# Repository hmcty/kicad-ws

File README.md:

# KiCad Workspace

This repository contains various KiCad hardware projects with an automated webviewer deployment.

## Projects

All KiCad projects are located in the `boards/` directory:
- `pedal_split_supply` - Pedal Split Supply

## Webviewer

An interactive webviewer is automatically built and deployed to GitHub Pages on every push to `main`.

**View the projects:** [https://hmcty.github.io/kicad-ws/](https://hmcty.github.io/kicad-ws/)

The webviewer allows you to:
- Browse all projects in the repository
- View schematics and PCB layouts interactively
- Download project files as ZIP archives
- Share links to specific locations in designs

## Deployment

The webviewer is built using [KiShare](https://github.com/hmcty/kishare) with [KiCanvas](https://github.com/theacodes/kicanvas) for rendering.

The deployment workflow (`.github/workflows/deploy.yml`) automatically:
1. Scans the repository for KiCad projects
2. Generates an interactive webviewer
3. Deploys to GitHub Pages

To trigger a manual rebuild, go to **Actions** → **Build and Deploy KiCad Webviewer** → **Run workflow**.

## Adding New Projects

Simply add new KiCad projects to the `boards/` directory and push to `main`. The webviewer will automatically rebuild and include the new projects.

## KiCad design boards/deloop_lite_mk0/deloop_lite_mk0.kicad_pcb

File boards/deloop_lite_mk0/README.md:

# Deloop Lite

System board for a simple, 2-track loop pedal.

Components:
- [Daisy Seed](https://electro-smith.com/products/daisy-seed)
  - Module carrying STM32H7 microcontroller, PCM3060 audio codec, and external
    SDRAM IC
- Barrel jack port assuming center-negative 9V DC power input
- +/-7V Power Supply
  - Imported design from a previous project, see [Pedal Split Supply](/#/project/pedal_split_supply)
- 2x 1/4" mono jacks (1 line-in, 1 line-out)
- 1x 3.5mm TRS MIDI input
- 2x audio input buffer (OPA2134)
- 2x audio output buffer (TL072)
- 1x output mix stage (TL072)
- 40-pin IDC header for UI and digital control connections
- 8x JST XH socket for auxiliary audio connections
- MicroSD card slot

The board is intended can be paired with different UI boards. Default signaling
assumes:
- 16x2 character LCD display
- Individually addressable RGB chain
- 3x footswitches
- 3x potentiometers (for track mixing)
- 1x rotary encoder (for menu navigation)
- 3x SPST switches

The board was designed to fit within a 1590DD enclosure.

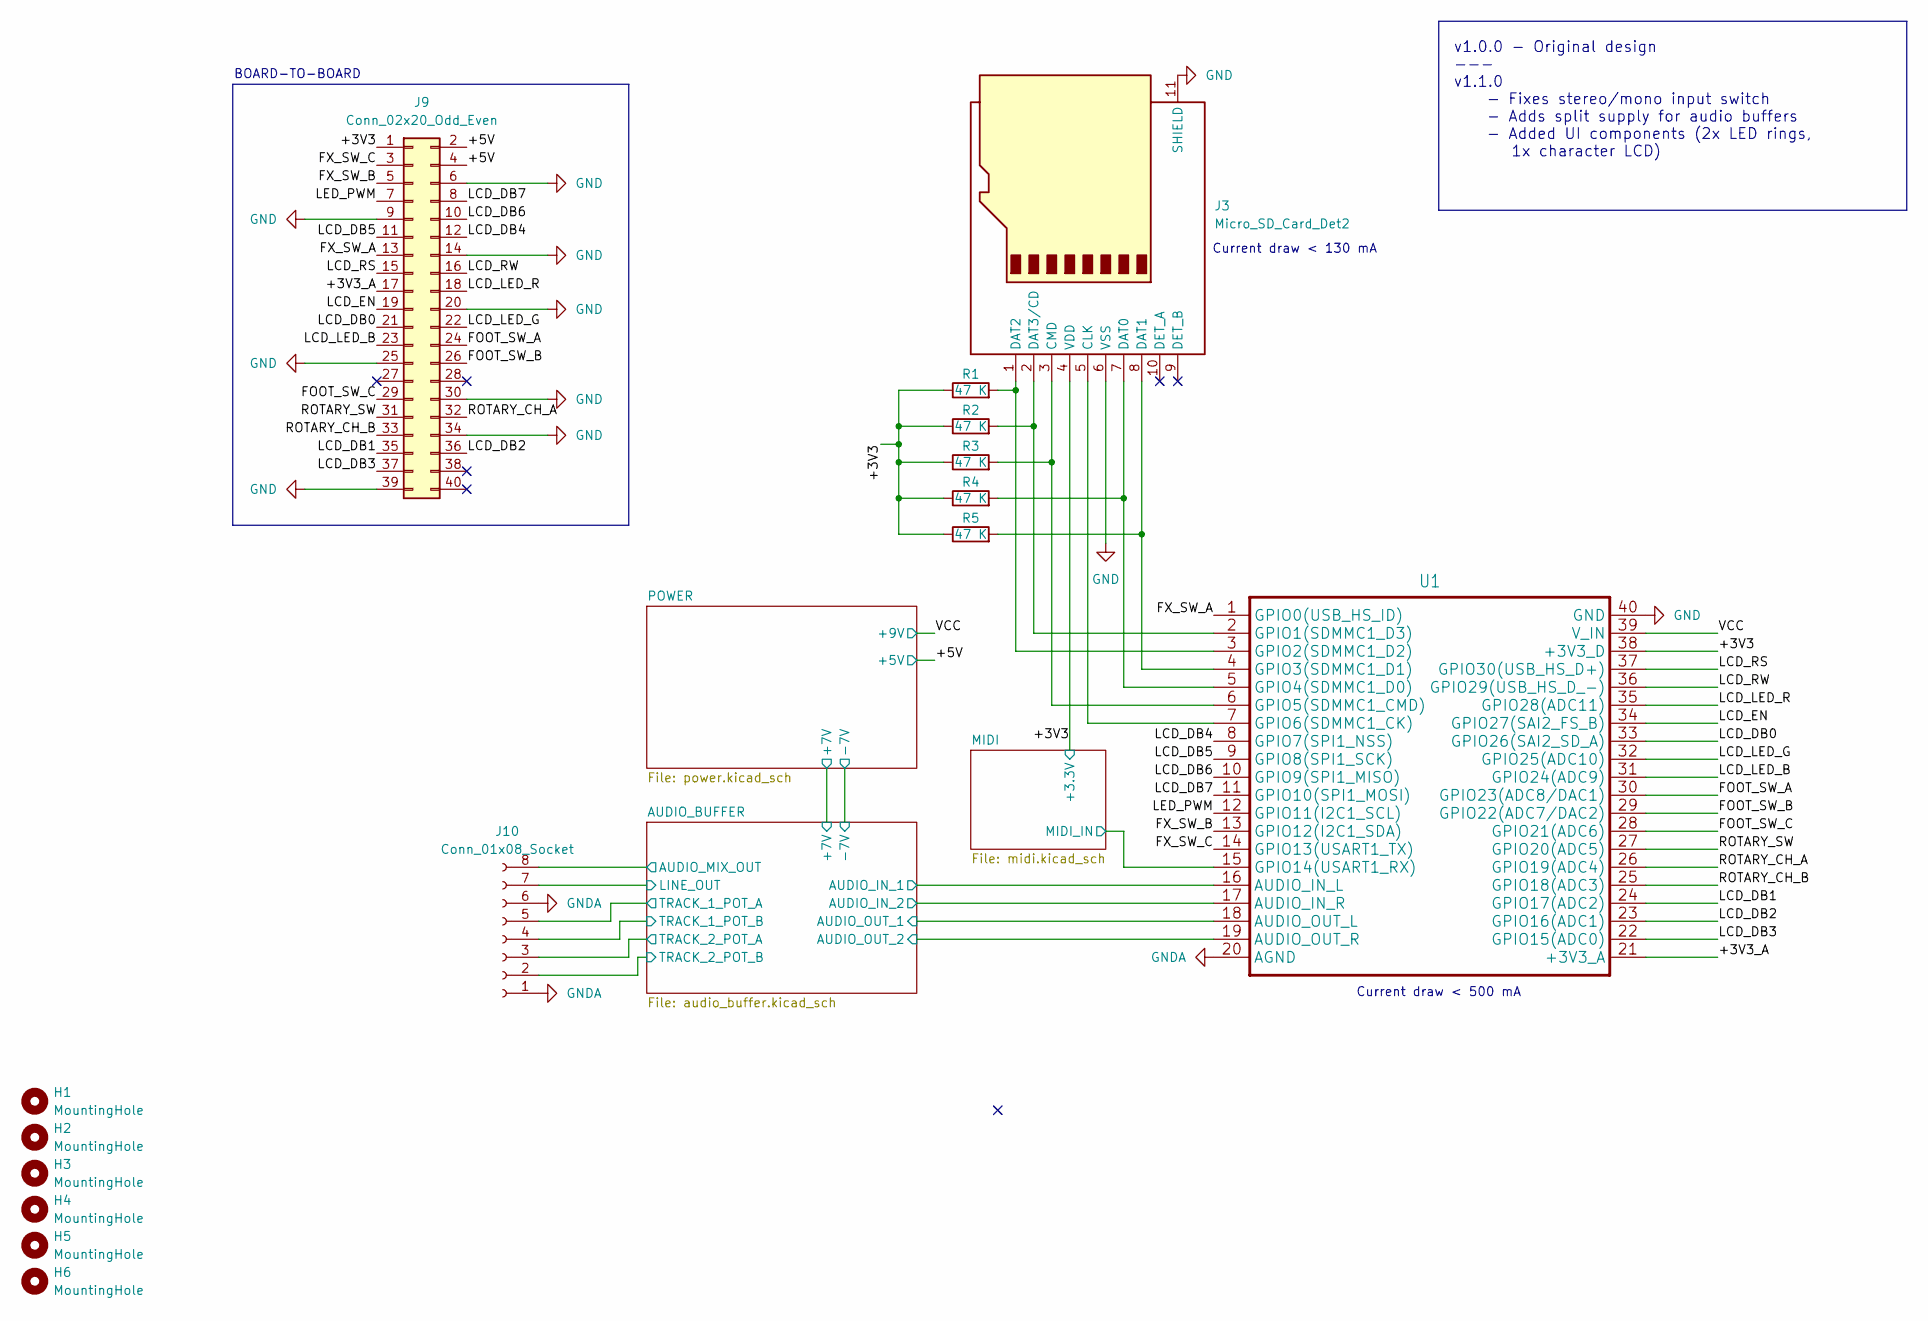
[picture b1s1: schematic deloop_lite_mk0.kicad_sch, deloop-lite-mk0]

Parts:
H1, H2, H3, H4, H5, H6: MountingHole; MountingHole_3.2mm_M3
J3: Micro_SD_Card_Det2; microSD_HC_Hirose_DM3AT-SF-PEJM5
J9: Conn_02x20_Odd_Even; IDC-Header_2x20_P2.54mm_Vertical
J10: Conn_01x08_Socket; JST_XH_B8B-XH-AM_1x08_P2.50mm_Vertical
R1, R2, R3, R4, R5: 47 K; R_0603_1608Metric_Pad0.98x0.95mm_HandSolder
U1: Electrosmith_Daisy_Seed

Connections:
/+3V3: J3.4 (VDD), J9.1, R1.1, R2.1, R3.1, R4.1, R5.1, U1.38 (+3V3_D); also elsewhere on the board
/+3V3_A: J9.17, U1.21 (+3V3_A)
/+5V: J9.2, J9.4; also elsewhere on the board
/AUDIO_BUFFER/AUDIO_IN_1: U1.16 (AUDIO_IN_L); also elsewhere on the board
/AUDIO_BUFFER/AUDIO_IN_2: U1.17 (AUDIO_IN_R); also elsewhere on the board
/AUDIO_BUFFER/AUDIO_MIX_OUT: J10.8; also elsewhere on the board
/AUDIO_BUFFER/AUDIO_OUT_1: U1.18 (AUDIO_OUT_L); also elsewhere on the board
/AUDIO_BUFFER/AUDIO_OUT_2: U1.19 (AUDIO_OUT_R); also elsewhere on the board
/AUDIO_BUFFER/LINE_OUT: J10.7; also elsewhere on the board
/AUDIO_BUFFER/TRACK_1_POT_A: J10.5; also elsewhere on the board
/AUDIO_BUFFER/TRACK_1_POT_B: J10.4; also elsewhere on the board
/AUDIO_BUFFER/TRACK_2_POT_A: J10.3; also elsewhere on the board
/AUDIO_BUFFER/TRACK_2_POT_B: J10.2; also elsewhere on the board
/FOOT_SW_A: J9.24, U1.30 (GPIO23(ADC8/DAC1))
/FOOT_SW_B: J9.26, U1.29 (GPIO22(ADC7/DAC2))
/FOOT_SW_C: J9.29, U1.28 (GPIO21(ADC6))
/FX_SW_A: J9.13, U1.1 (GPIO0(USB_HS_ID))
/FX_SW_B: J9.5, U1.13 (GPIO12(I2C1_SDA))
/FX_SW_C: J9.3, U1.14 (GPIO13(USART1_TX))
/LCD_DB0: J9.21, U1.33 (GPIO26(SAI2_SD_A))
/LCD_DB1: J9.35, U1.24 (GPIO17(ADC2))
/LCD_DB2: J9.36, U1.23 (GPIO16(ADC1))
/LCD_DB3: J9.37, U1.22 (GPIO15(ADC0))
/LCD_DB4: J9.12, U1.8 (GPIO7(SPI1_NSS))
/LCD_DB5: J9.11, U1.9 (GPIO8(SPI1_SCK))
/LCD_DB6: J9.10, U1.10 (GPIO9(SPI1_MISO))
/LCD_DB7: J9.8, U1.11 (GPIO10(SPI1_MOSI))
/LCD_EN: J9.19, U1.34 (GPIO27(SAI2_FS_B))
/LCD_LED_B: J9.23, U1.31 (GPIO24(ADC9))
/LCD_LED_G: J9.22, U1.32 (GPIO25(ADC10))
/LCD_LED_R: J9.18, U1.35 (GPIO28(ADC11))
/LCD_RS: J9.15, U1.37 (GPIO30(USB_HS_D+))
/LCD_RW: J9.16, U1.36 (GPIO29(USB_HS_D_-))
/LED_PWM: J9.7, U1.12 (GPIO11(I2C1_SCL))
/MIDI/MIDI_IN: U1.15 (GPIO14(USART1_RX)); also elsewhere on the board
/ROTARY_CH_A: J9.32, U1.26 (GPIO19(ADC4))
/ROTARY_CH_B: J9.33, U1.25 (GPIO18(ADC3))
/ROTARY_SW: J9.31, U1.27 (GPIO20(ADC5))
/VCC: U1.39 (V_IN); also elsewhere on the board
GND: J3.6 (VSS), J3.11 (SHIELD), J9.6, J9.9, J9.14, J9.20, J9.25, J9.30, J9.34, J9.39, U1.40 (GND); also elsewhere on the board
GNDA: J10.1, J10.6, U1.20 (AGND); also elsewhere on the board
unnamed: J3.5 (CLK), U1.7 (GPIO6(SDMMC1_CK))
unnamed: J3.3 (CMD), R3.2, U1.6 (GPIO5(SDMMC1_CMD))
unnamed: J3.7 (DAT0), R4.2, U1.5 (GPIO4(SDMMC1_D0))
unnamed: J3.8 (DAT1), R5.2, U1.4 (GPIO3(SDMMC1_D1))
unnamed: J3.1 (DAT2), R1.2, U1.3 (GPIO2(SDMMC1_D2))
unnamed: J3.2 (DAT3/CD), R2.2, U1.2 (GPIO1(SDMMC1_D3))

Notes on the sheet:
BOARD-TO-BOARD
Current draw < 500 mA
Current draw < 130 mA
v1.0.0 - Original design --- v1.1.0 - Fixes stereo/mono input switch - Adds split supply for audio buffers - Added UI components (2x LED rings, 1x character LCD)

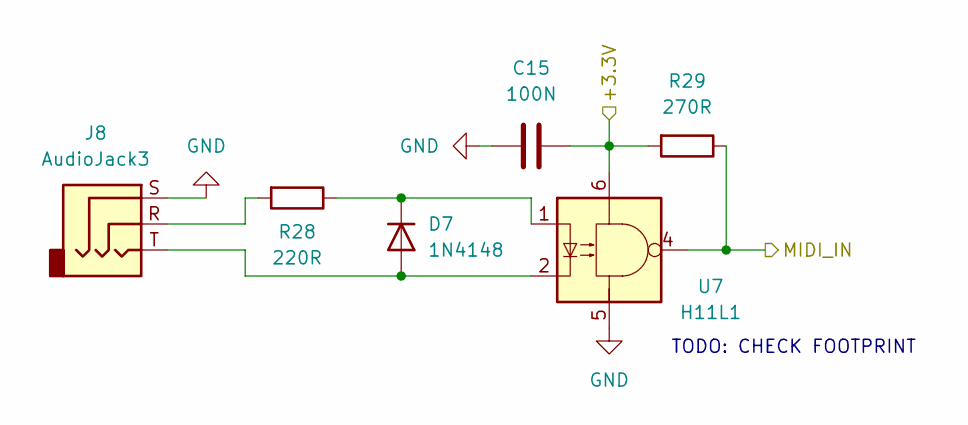
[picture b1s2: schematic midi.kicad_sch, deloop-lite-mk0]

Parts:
C15: 100N; C_0603_1608Metric_Pad1.08x0.95mm_HandSolder
D7: 1N4148; Nexperia_CFP3_SOD-123W
J8: AudioJack3; Jack_3.5mm_CUI_SJ1-3523N_Horizontal
R28: 220R; R_0603_1608Metric_Pad0.98x0.95mm_HandSolder
R29: 270R; R_0603_1608Metric_Pad0.98x0.95mm_HandSolder
U7: H11L1; SMDIP-6_W9.53mm

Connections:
/+3V3: C15.2, R29.2, U7.6; also elsewhere on the board
/MIDI/MIDI_IN: R29.1, U7.4; also elsewhere on the board
GND: C15.1, J8.S, U7.5; also elsewhere on the board
unnamed: D7.2 (A), J8.T, U7.2
unnamed: D7.1 (K), R28.1, U7.1
unnamed: J8.R, R28.2

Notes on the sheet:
TODO: CHECK FOOTPRINT

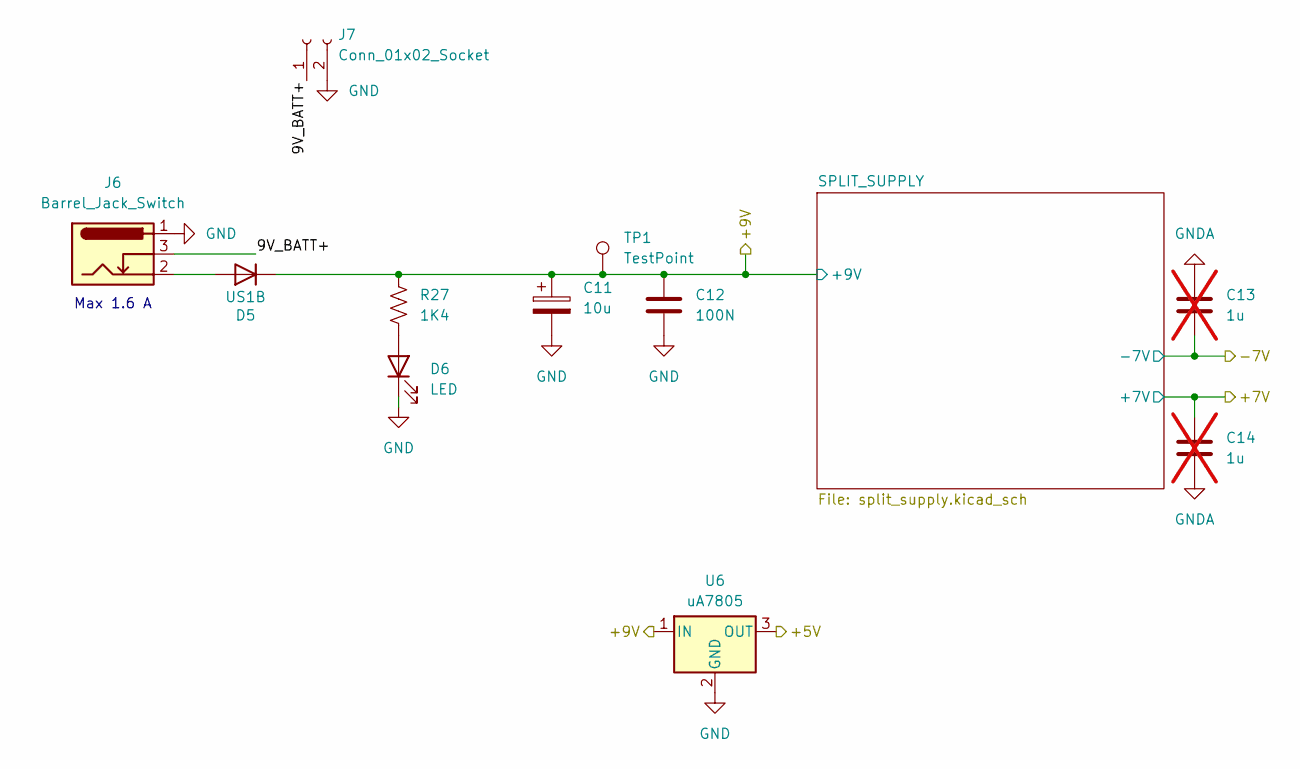
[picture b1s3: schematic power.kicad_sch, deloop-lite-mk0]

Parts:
C11: 10u; CP_Radial_D5.0mm_P2.00mm
C12: 100N; C_0603_1608Metric_Pad1.08x0.95mm_HandSolder
C13, C14: 1u; C_1206_3216Metric_Pad1.33x1.80mm_HandSolder; not fitted
D5: US1B; D_SMA
D6: LED; LED_1206_3216Metric_Pad1.42x1.75mm_HandSolder
J6: Barrel_Jack_Switch; BarrelJack_Horizontal
J7: Conn_01x02_Socket; SolderWire-1.5sqmm_1x02_P7.8mm_D1.7mm_OD3.9mm
R27: 1K4; R_0603_1608Metric_Pad0.98x0.95mm_HandSolder
TP1: TestPoint; TestPoint_Pad_4.0x4.0mm
U6: uA7805; TO-263-2

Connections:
/+5V: U6.3 (OUT); also elsewhere on the board
/AUDIO_BUFFER/+7V: C14.2; also elsewhere on the board
/AUDIO_BUFFER/-7V: C13.1; also elsewhere on the board
/POWER/9V_BATT+: J6.3, J7.1
/VCC: C11.1, C12.1, D5.1 (K), R27.1, TP1.1, U6.1 (IN); also elsewhere on the board
GND: C11.2, C12.2, D6.1 (K), J6.1, J7.2, U6.2 (GND); also elsewhere on the board
GNDA: C13.2, C14.1; also elsewhere on the board
unnamed: D5.2 (A), J6.2
unnamed: D6.2 (A), R27.2

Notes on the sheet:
Max 1.6 A

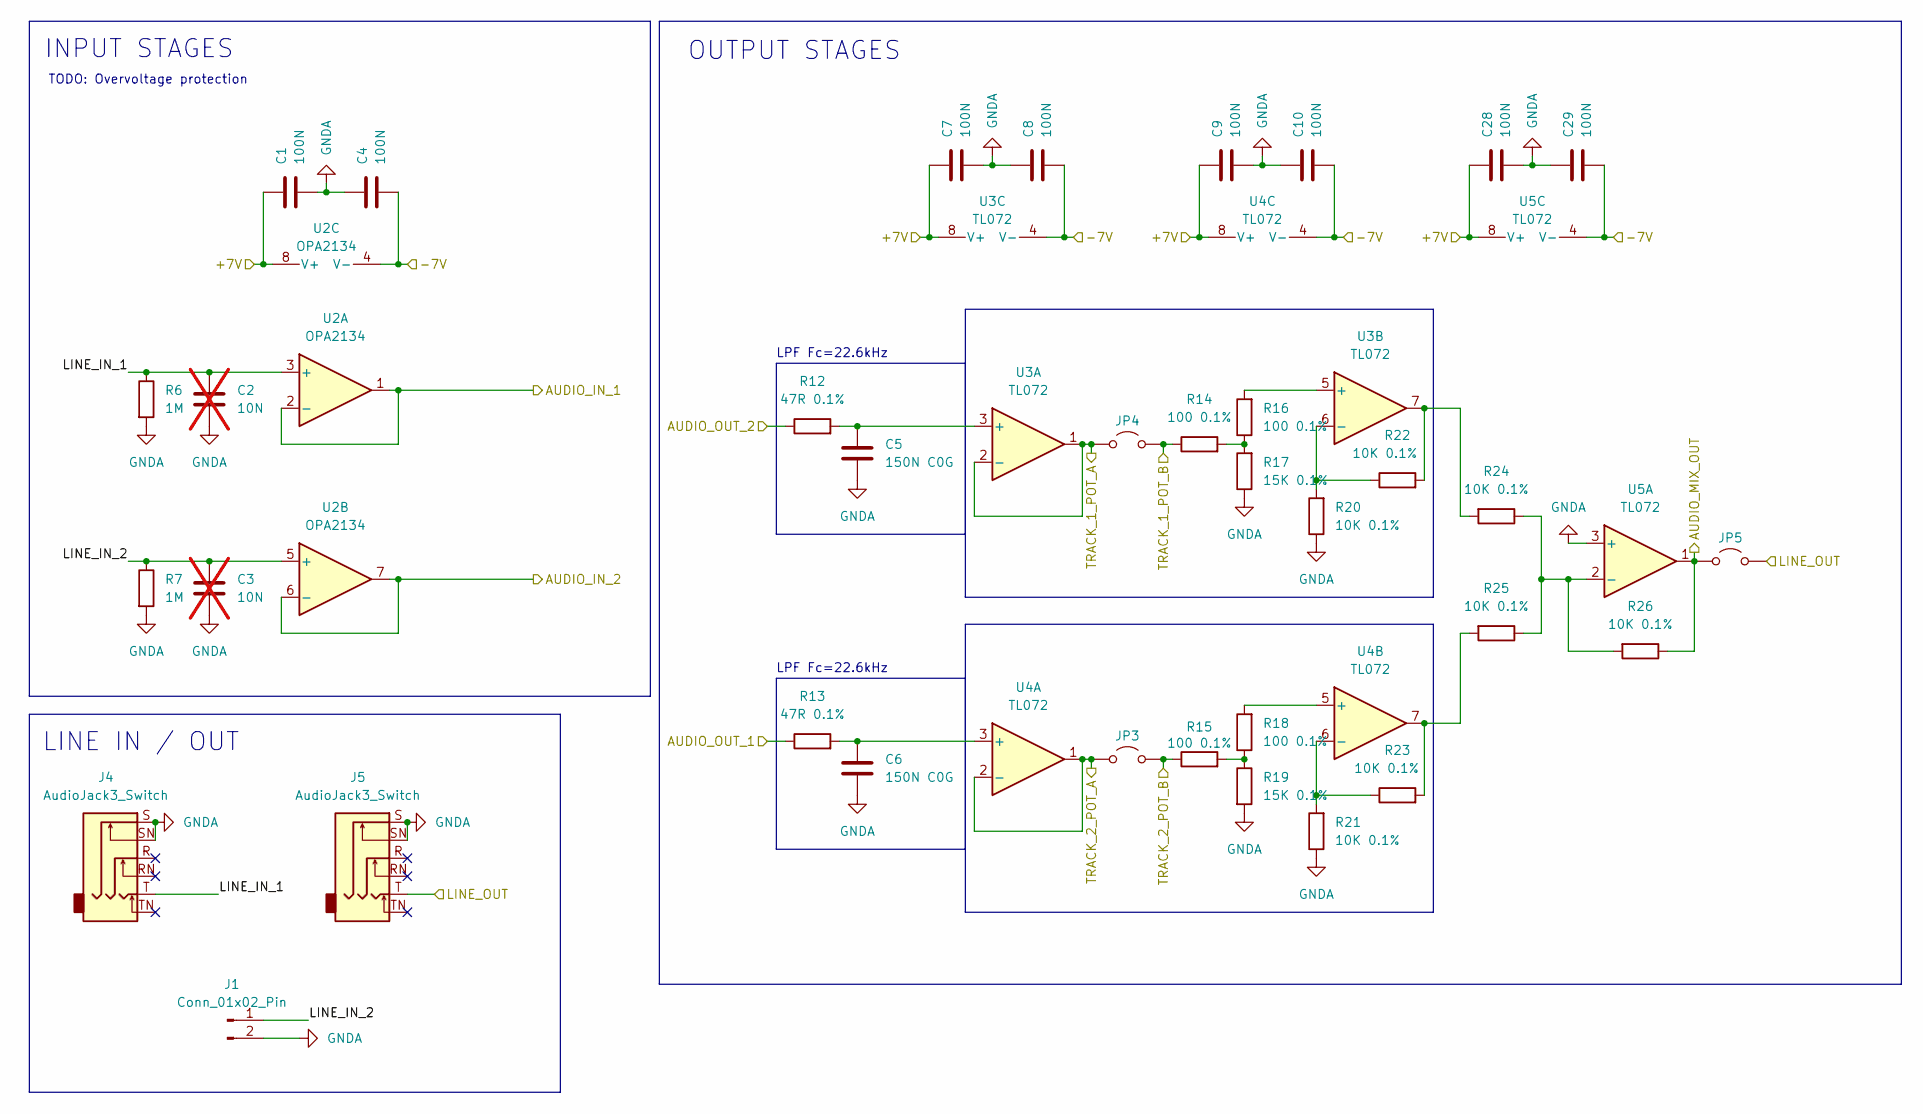
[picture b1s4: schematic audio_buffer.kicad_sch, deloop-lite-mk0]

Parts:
C1, C4, C7, C8, C9, C10, C28, C29: 100N; C_0603_1608Metric_Pad1.08x0.95mm_HandSolder
C2, C3: 10N; C_0603_1608Metric_Pad1.08x0.95mm_HandSolder; not fitted
C5, C6: 150N C0G; C_1812_4532Metric_Pad1.57x3.40mm_HandSolder
J1: Conn_01x02_Pin; PinHeader_1x02_P2.54mm_Vertical
J4, J5: AudioJack3_Switch; Jack_6.35mm_Neutrik_NMJ6HCD2_Horizontal
JP3, JP4, JP5: Jumper_2_Open; PinHeader_1x02_P2.54mm_Vertical
R6, R7: 1M; R_0603_1608Metric_Pad0.98x0.95mm_HandSolder
R12, R13: 47R 0.1%; R_0603_1608Metric_Pad0.98x0.95mm_HandSolder
R14, R15, R16, R18: 100 0.1%; R_0603_1608Metric_Pad0.98x0.95mm_HandSolder
R17, R19: 15K 0.1%; R_0603_1608Metric_Pad0.98x0.95mm_HandSolder
R20, R21, R22, R23, R24, R25, R26: 10K 0.1%; R_0603_1608Metric_Pad0.98x0.95mm_HandSolder
U2: OPA2134; SOIC-8_3.9x4.9mm_P1.27mm
U3, U4: TL072; SOIC-8_3.9x4.9mm_P1.27mm
U5: TL072

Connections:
/AUDIO_BUFFER/+7V: C1.2, C7.2, C9.2, C28.2, U2.8 (V+), U3.8 (V+), U4.8 (V+), U5.8 (V+); also elsewhere on the board
/AUDIO_BUFFER/-7V: C4.1, C8.1, C10.1, C29.1, U2.4 (V-), U3.4 (V-), U4.4 (V-), U5.4 (V-); also elsewhere on the board
/AUDIO_BUFFER/AUDIO_IN_1: U2.1, U2.2 (-); also elsewhere on the board
/AUDIO_BUFFER/AUDIO_IN_2: U2.6 (-), U2.7; also elsewhere on the board
/AUDIO_BUFFER/AUDIO_MIX_OUT: JP5.1 (A), R26.1, U5.1; also elsewhere on the board
/AUDIO_BUFFER/AUDIO_OUT_1: R13.1; also elsewhere on the board
/AUDIO_BUFFER/AUDIO_OUT_2: R12.1; also elsewhere on the board
/AUDIO_BUFFER/LINE_IN_1: C2.1, J4.T, R6.1, U2.3 (+)
/AUDIO_BUFFER/LINE_IN_2: C3.1, J1.1, R7.1, U2.5 (+)
/AUDIO_BUFFER/LINE_OUT: J5.T, JP5.2 (B); also elsewhere on the board
/AUDIO_BUFFER/TRACK_1_POT_A: JP4.1 (A), U3.1, U3.2 (-); also elsewhere on the board
/AUDIO_BUFFER/TRACK_1_POT_B: JP4.2 (B), R14.1; also elsewhere on the board
/AUDIO_BUFFER/TRACK_2_POT_A: JP3.1 (A), U4.1, U4.2 (-); also elsewhere on the board
/AUDIO_BUFFER/TRACK_2_POT_B: JP3.2 (B), R15.1; also elsewhere on the board
GNDA: C1.1, C2.2, C3.2, C4.2, C5.1, C6.2, C7.1, C8.2, C9.1, C10.2, C28.1, C29.2, J1.2, J4.S, J4.SN, J5.S, J5.SN, R6.2, R7.2, R17.1, R19.2, R20.1, R21.1, U5.3 (+); also elsewhere on the board
unnamed: R14.2, R16.1, R17.2
unnamed: R15.2, R18.1, R19.1
unnamed: R22.2, R24.2, U3.7
unnamed: R23.2, R25.2, U4.7
unnamed: C5.2, R12.2, U3.3 (+)
unnamed: R16.2, U3.5 (+)
unnamed: R20.2, R22.1, U3.6 (-)
unnamed: C6.1, R13.2, U4.3 (+)
unnamed: R18.2, U4.5 (+)
unnamed: R21.2, R23.1, U4.6 (-)
unnamed: R24.1, R25.1, R26.2, U5.2 (-)

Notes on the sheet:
LPF Fc=22.6kHz
INPUT STAGES
TODO: Overvoltage protection
OUTPUT STAGES
LINE IN / OUT

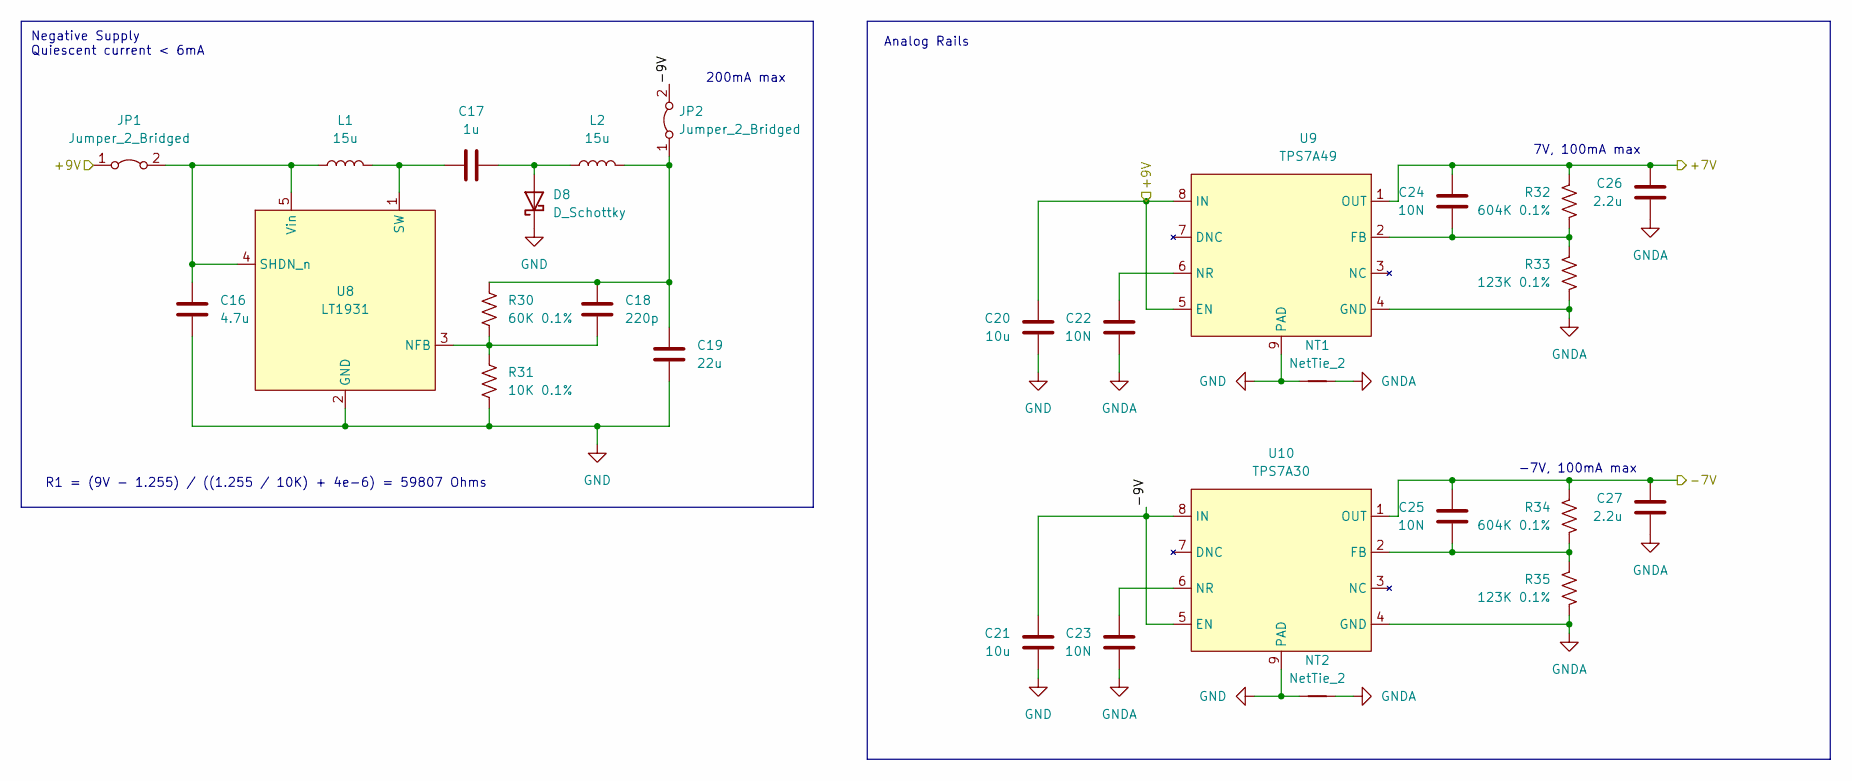
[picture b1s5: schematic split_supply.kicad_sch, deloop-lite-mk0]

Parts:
C16: 4.7u; C_0805_2012Metric_Pad1.18x1.45mm_HandSolder
C17: 1u; C_1206_3216Metric_Pad1.33x1.80mm_HandSolder
C18: 220p; C_0805_2012Metric_Pad1.18x1.45mm_HandSolder
C19: 22u; C_0805_2012Metric_Pad1.18x1.45mm_HandSolder
C20, C21: 10u; C_1206_3216Metric_Pad1.33x1.80mm_HandSolder
C22, C23, C24, C25: 10N; C_0805_2012Metric_Pad1.18x1.45mm_HandSolder
C26, C27: 2.2u; C_0805_2012Metric_Pad1.18x1.45mm_HandSolder
D8: D_Schottky; C_1206_3216Metric_Pad1.33x1.80mm_HandSolder
JP1, JP2: Jumper_2_Bridged; PinHeader_1x02_P2.54mm_Vertical
L1, L2: 15u; L_1812_4532Metric_Pad1.30x3.40mm_HandSolder
NT1, NT2: NetTie_2; NetTie-2_SMD_Pad2.0mm
R30: 60K 0.1%; R_0603_1608Metric_Pad0.98x0.95mm_HandSolder
R31: 10K 0.1%; R_0603_1608Metric_Pad0.98x0.95mm_HandSolder
R32, R34: 604K 0.1%; R_0603_1608Metric_Pad0.98x0.95mm_HandSolder
R33, R35: 123K 0.1%; R_0603_1608Metric_Pad0.98x0.95mm_HandSolder
U8: LT1931; TSOT-23-5_HandSoldering
U9: TPS7A49; MSOP-8-1EP_3x3mm_P0.65mm_EP1.68x1.88mm_ThermalVias
U10: TPS7A30; MSOP-8-1EP_3x3mm_P0.65mm_EP1.68x1.88mm_ThermalVias

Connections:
/AUDIO_BUFFER/+7V: C24.1, C26.1, R32.1, U9.1 (OUT); also elsewhere on the board
/AUDIO_BUFFER/-7V: C25.2, C27.1, R34.1, U10.1 (OUT); also elsewhere on the board
/POWER/SPLIT_SUPPLY/-9V: C21.1, JP2.2 (B), U10.5 (EN), U10.8 (IN)
/VCC: C20.1, JP1.1 (A), U9.5 (EN), U9.8 (IN); also elsewhere on the board
GND: C16.2, C19.2, C20.2, C21.2, D8.1 (K), NT1.1, NT2.1, R31.2, U8.2 (GND), U9.9 (PAD), U10.9 (PAD); also elsewhere on the board
GNDA: C22.2, C23.2, C26.2, C27.2, NT1.2, NT2.2, R33.2, R35.1, U9.4 (GND), U10.4 (GND); also elsewhere on the board
unnamed: C17.2, D8.2 (A), L2.2
unnamed: C16.1, JP1.2 (B), L1.1, U8.4 (SHDN_n), U8.5 (Vin)
unnamed: C18.1, C19.1, JP2.1 (A), L2.1, R30.1
unnamed: C18.2, R30.2, R31.1, U8.3 (NFB)
unnamed: C17.1, L1.2, U8.1 (SW)
unnamed: C24.2, R32.2, R33.1, U9.2 (FB)
unnamed: C22.1, U9.6 (NR)
unnamed: C25.1, R34.2, R35.2, U10.2 (FB)
unnamed: C23.1, U10.6 (NR)

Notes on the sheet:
R1 = (9V - 1.255) / ((1.255 / 10K) + 4e-6) = 59807 Ohms
200mA max
Analog Rails
Negative Supply Quiescent current < 6mA
-7V, 100mA max
7V, 100mA max

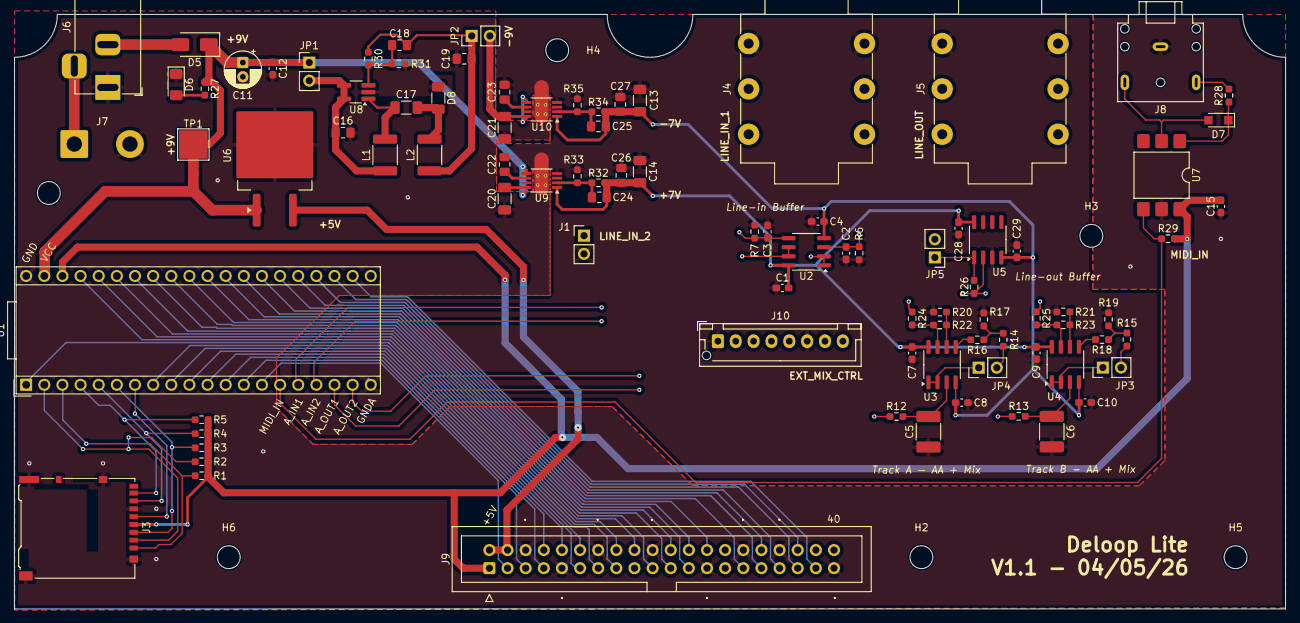
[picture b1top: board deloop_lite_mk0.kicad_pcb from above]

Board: 4 copper layers, 178.0 x 83.3 mm, 99 parts (0 on the bottom side), 78 nets.

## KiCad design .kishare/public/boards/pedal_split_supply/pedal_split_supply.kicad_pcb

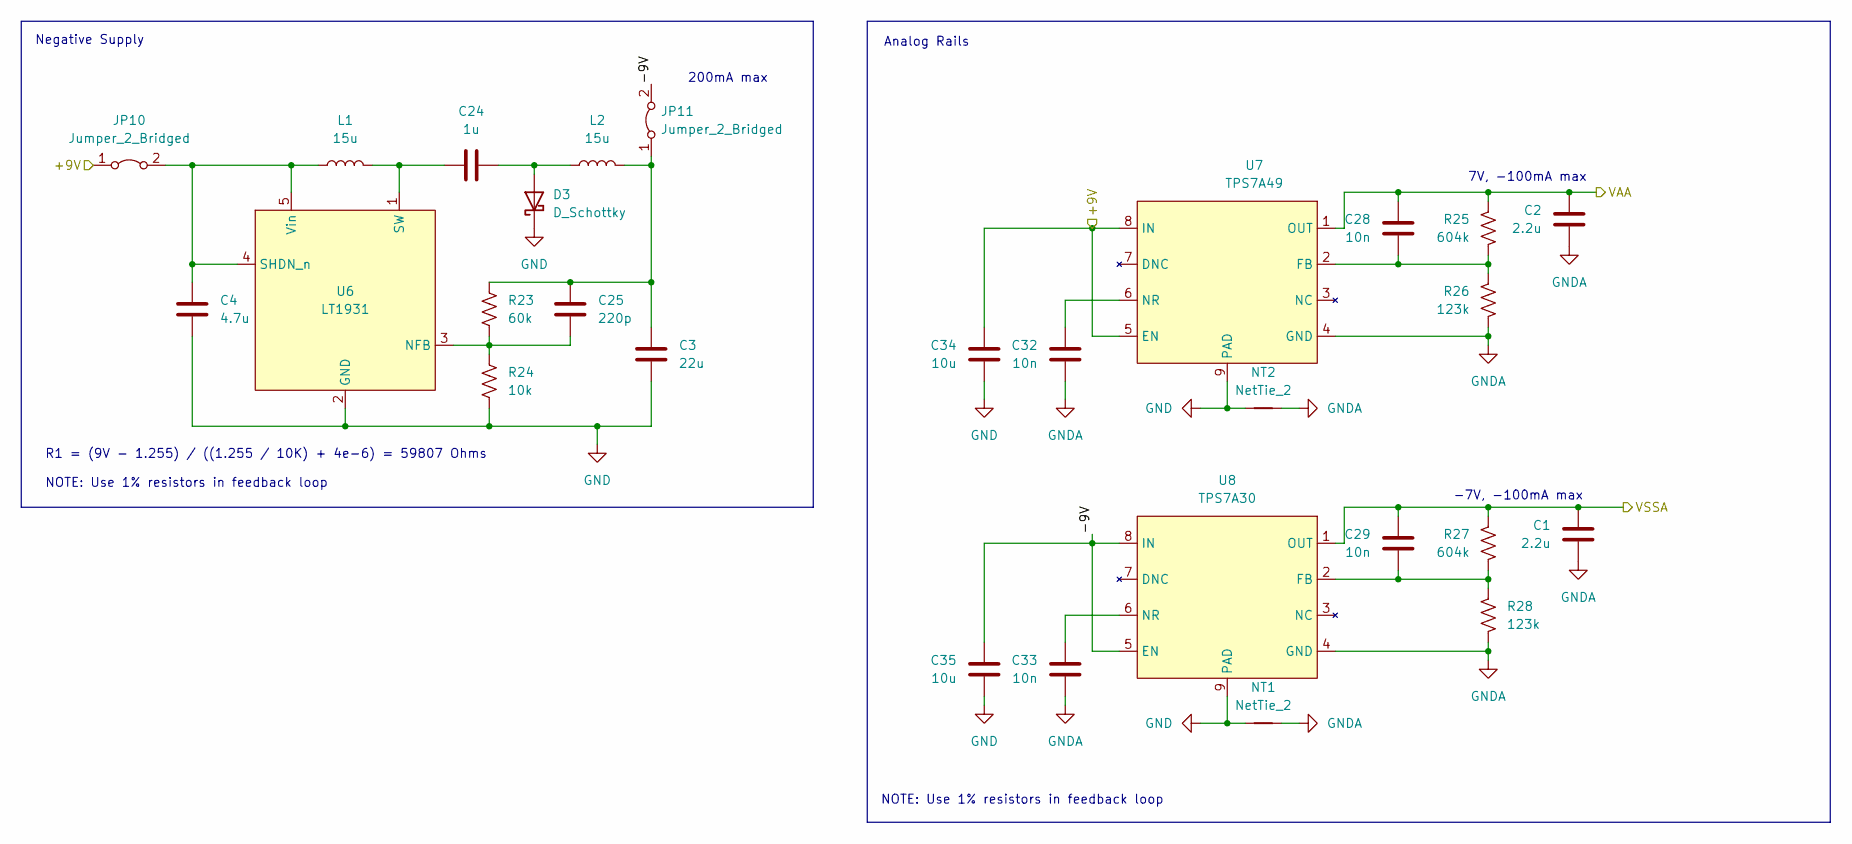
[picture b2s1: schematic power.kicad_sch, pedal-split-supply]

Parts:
C1, C2: 2.2u; C_0805_2012Metric_Pad1.18x1.45mm_HandSolder
C3: 22u; C_0805_2012Metric_Pad1.18x1.45mm_HandSolder
C4: 4.7u; C_0805_2012Metric_Pad1.18x1.45mm_HandSolder
C24: 1u; C_1206_3216Metric_Pad1.33x1.80mm_HandSolder
C25: 220p; C_0805_2012Metric_Pad1.18x1.45mm_HandSolder
C28, C29, C32, C33: 10n; C_0805_2012Metric_Pad1.18x1.45mm_HandSolder
C34, C35: 10u; C_1206_3216Metric_Pad1.33x1.80mm_HandSolder
D3: D_Schottky; C_1206_3216Metric_Pad1.33x1.80mm_HandSolder
JP10, JP11: Jumper_2_Bridged; PinHeader_1x02_P2.54mm_Vertical
L1, L2: 15u; L_1812_4532Metric_Pad1.30x3.40mm_HandSolder
NT1, NT2: NetTie_2; NetTie-2_SMD_Pad2.0mm
R23: 60k; R_1206_3216Metric_Pad1.30x1.75mm_HandSolder
R24: 10k; R_1206_3216Metric_Pad1.30x1.75mm_HandSolder
R25, R27: 604k; R_1206_3216Metric_Pad1.30x1.75mm_HandSolder
R26, R28: 123k; R_1206_3216Metric_Pad1.30x1.75mm_HandSolder
U6: LT1931; TSOT-23-5_HandSoldering
U7: TPS7A49; MSOP-8-1EP_3x3mm_P0.65mm_EP1.68x1.88mm_ThermalVias
U8: TPS7A30; MSOP-8-1EP_3x3mm_P0.65mm_EP1.68x1.88mm_ThermalVias

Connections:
/POWER/+9V: C34.1, JP10.1 (A), U7.5 (EN), U7.8 (IN); also elsewhere on the board
/POWER/-9V: C35.1, JP11.2 (B), U8.5 (EN), U8.8 (IN)
/POWER/VAA: C2.1, C28.1, R25.1, U7.1 (OUT); also elsewhere on the board
/POWER/VSSA: C1.1, C29.1, R27.1, U8.1 (OUT); also elsewhere on the board
GND: C3.2, C4.2, C34.2, C35.2, D3.1 (K), NT1.1, NT2.1, R24.2, U6.2 (GND), U7.9 (PAD), U8.9 (PAD); also elsewhere on the board
GNDA: C1.2, C2.2, C32.2, C33.2, NT1.2, NT2.2, R26.2, R28.2, U7.4 (GND), U8.4 (GND)
unnamed: C24.2, D3.2 (A), L2.2
unnamed: C4.1, JP10.2 (B), L1.1, U6.4 (SHDN_n), U6.5 (Vin)
unnamed: C3.1, C25.1, JP11.1 (A), L2.1, R23.1
unnamed: C25.2, R23.2, R24.1, U6.3 (NFB)
unnamed: C24.1, L1.2, U6.1 (SW)
unnamed: C28.2, R25.2, R26.1, U7.2 (FB)
unnamed: C32.1, U7.6 (NR)
unnamed: C29.2, R27.2, R28.1, U8.2 (FB)
unnamed: C33.1, U8.6 (NR)

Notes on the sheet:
R1 = (9V - 1.255) / ((1.255 / 10K) + 4e-6) = 59807 Ohms NOTE: Use 1% resistors in feedback loop
Negative Supply
NOTE: Use 1% resistors in feedback loop
-7V, -100mA max
200mA max
Analog Rails
7V, -100mA max

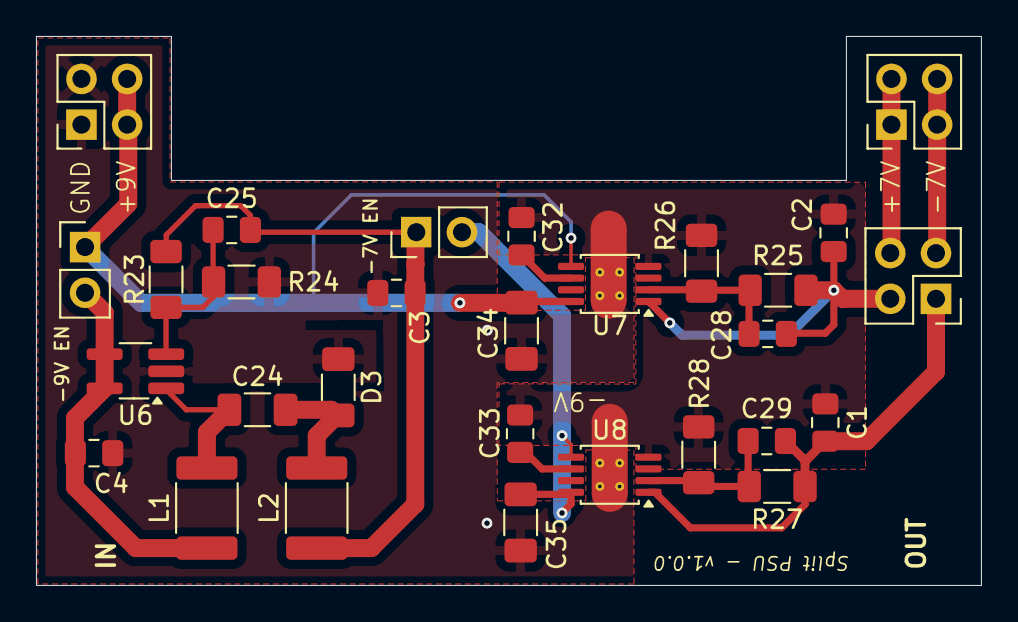
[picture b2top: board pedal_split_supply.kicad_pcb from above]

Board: 2 copper layers, 52.5 x 30.5 mm, 31 parts (0 on the bottom side), 17 nets.

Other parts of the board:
J1: Conn_02x02_Top_Bottom; PinHeader_2x02_P2.54mm_Vertical
J3, J5: Conn_02x02_Top_Bottom; PinSocket_2x02_P2.54mm_Vertical

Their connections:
/POWER/+9V: J3.2, J3.4; also elsewhere on the board
/POWER/VAA: J1.2; also elsewhere on the board
/POWER/VSSA: J1.1; also elsewhere on the board
GND: J3.1, J3.3; also elsewhere on the board
unnamed: J1.3, J5.2, J5.4
unnamed: J1.4, J5.1, J5.3

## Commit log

2026-04-07 init
2026-04-07 removed
2026-04-08 use latest kisite
2026-04-08 updated docs
2026-04-08 Added LICENSE
2026-04-09 Add LICENSE file
